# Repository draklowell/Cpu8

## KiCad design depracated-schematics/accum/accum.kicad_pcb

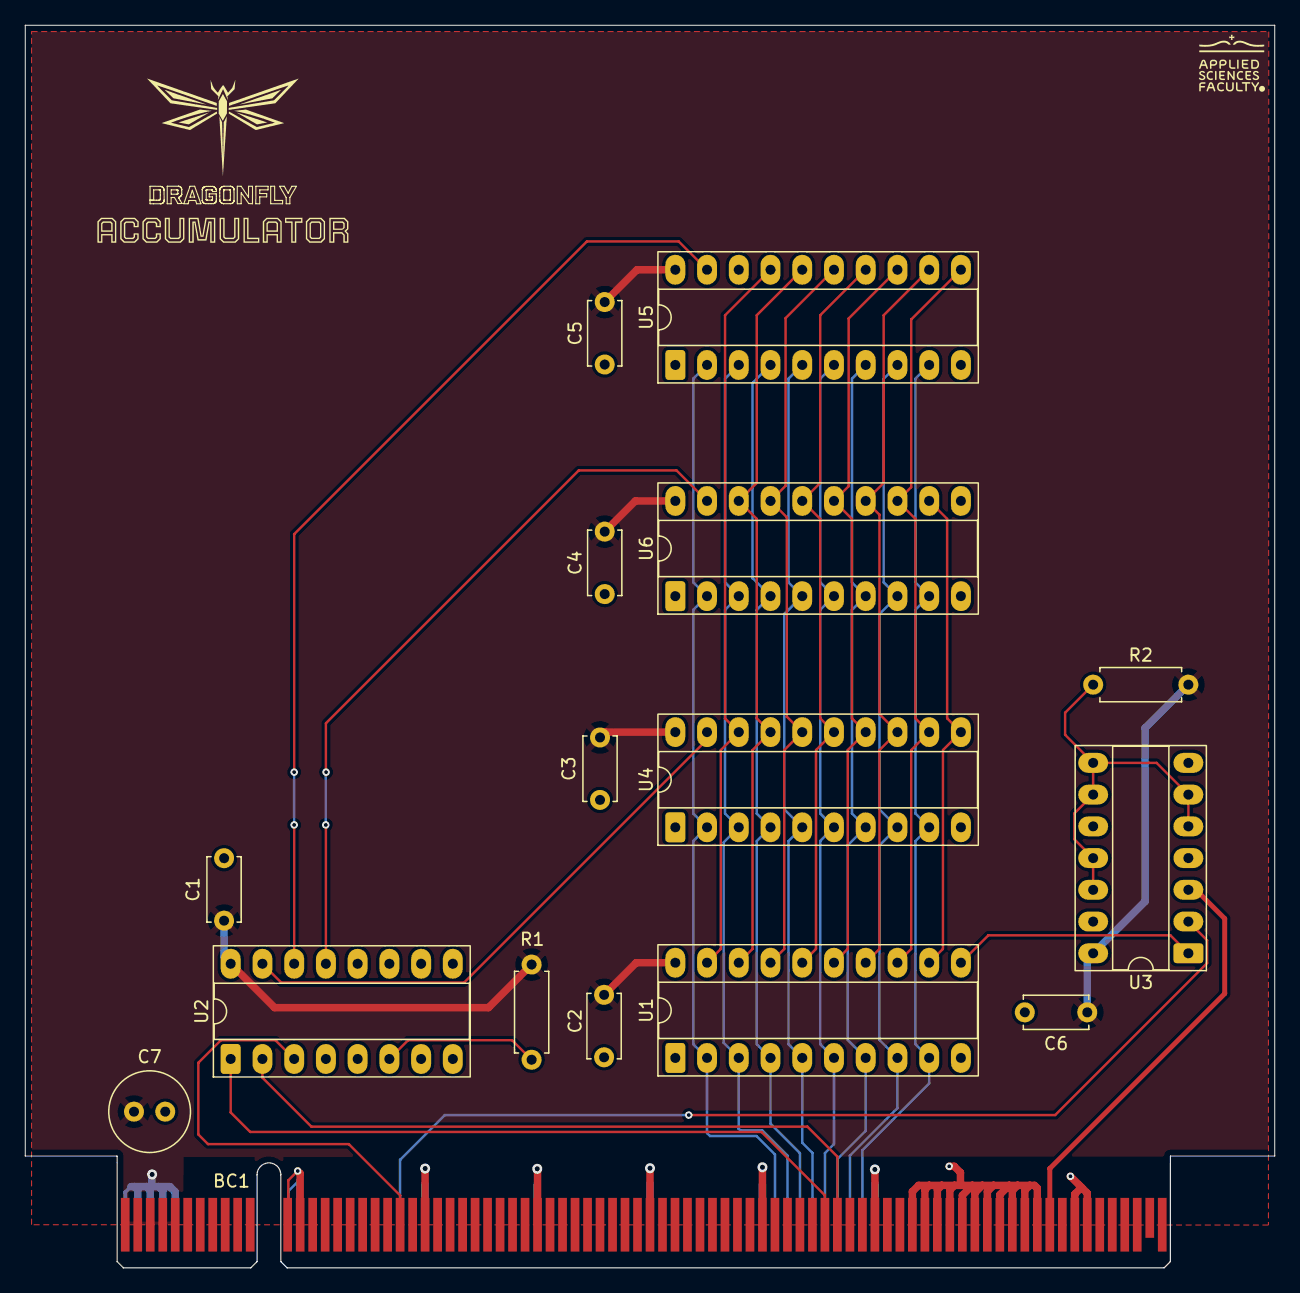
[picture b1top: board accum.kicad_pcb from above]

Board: 2 copper layers, 100.0 x 99.4 mm, 17 parts (0 on the bottom side), 29 nets.

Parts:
BC1: BusConnector; BUS_PCIexpress_x16
C1, C2, C3, C4, C5, C6: C; C_Disc_D5.0mm_W2.5mm_P5.00mm
C7: C; C_Radial_D6.3mm_H5.0mm_P2.50mm
R1, R2: R; R_Axial_DIN0207_L6.3mm_D2.5mm_P7.62mm_Horizontal
U1: 74LS574; DIP-20_W7.62mm_Socket_LongPads
U2: 74LS138; DIP-16_W7.62mm_Socket_LongPads
U3: 74LS02; DIP-14_W7.62mm_Socket_LongPads
U4, U5, U6: 74LS245; DIP-20_W7.62mm_Socket_LongPads
kibuzzard-6911C8C8: G***; kibuzzard-6911C8C8

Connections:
/ACCUM0: U1.19 (Q0), U4.18 (B0), U5.17 (B1)
/ACCUM1: U1.18 (Q1), U4.17 (B1), U5.16 (B2), U6.18 (B0)
/ACCUM2: U1.17 (Q2), U4.16 (B2), U5.15 (B3), U6.17 (B1)
/ACCUM3: U1.16 (Q3), U4.15 (B3), U5.14 (B4), U6.16 (B2)
/ACCUM4: U1.15 (Q4), U4.14 (B4), U5.13 (B5), U6.15 (B3)
/ACCUM5: U1.14 (Q5), U4.13 (B5), U5.12 (B6), U6.14 (B4)
/ACCUM6: U1.13 (Q6), U4.12 (B6), U5.11 (B7), U6.13 (B5)
/ACCUM7: U1.12 (Q7), U4.11 (B7), U6.12 (B6)
/ACSHLEFT: U2.14 (O1), U5.19 (CE)
/ACSHRIGHT: U2.13 (O2), U6.19 (CE)
/DATA0: BC1.A51 (DATA0), U1.2 (D0), U4.2 (A0), U5.2 (A0), U6.2 (A0)
/DATA1: BC1.A52 (DATA1), U1.3 (D1), U4.3 (A1), U5.3 (A1), U6.3 (A1)
/DATA2: BC1.A53 (DATA2), U1.4 (D2), U4.4 (A2), U5.4 (A2), U6.4 (A2)
/DATA3: BC1.A54 (DATA3), U1.5 (D3), U4.5 (A3), U5.5 (A3), U6.5 (A3)
/DATA4: BC1.A55 (DATA4), U1.6 (D4), U4.6 (A4), U5.6 (A4), U6.6 (A4)
/DATA5: BC1.A56 (DATA5), U1.7 (D5), U4.7 (A5), U5.7 (A5), U6.7 (A5)
/DATA6: BC1.A57 (DATA6), U1.8 (D6), U4.8 (A6), U5.8 (A6), U6.8 (A6)
/DATA7: BC1.A58 (DATA7), U1.9 (D7), U4.9 (A7), U5.9 (A7), U6.9 (A7)
/LAC: BC1.A21 (~LAC), U3.2
/SHL: BC1.B55 (ACSHLEFT), U2.1 (A0)
/SHR: BC1.B56 (ACSHRIGHT), U2.2 (A1)
/~CLK: BC1.B73 (~CLK), U3.3
/~PASS: BC1.B21 (~RAC), U2.3 (A2)
/~RAC: U2.15 (O0), U4.19 (CE)
GND: BC1.A12 (GND), BC1.A13 (GND), BC1.A23 (GND), BC1.A32 (GND), BC1.A41 (GND), BC1.A50 (GND), BC1.A59 (GND), BC1.A63 (GND), BC1.A64 (GND), BC1.A65 (GND), BC1.A66 (GND), BC1.A70 (GND), BC1.A71 (GND), BC1.A72 (GND), BC1.A73 (GND), BC1.A74 (GND), BC1.A75 (GND), BC1.A76 (GND), BC1.B12 (GND), BC1.B13 (GND), BC1.B23 (GND), BC1.B32 (GND), BC1.B41 (GND), BC1.B50 (GND), BC1.B59 (GND), BC1.B62 (GND), BC1.B63 (GND), BC1.B64 (GND), BC1.B65 (GND), BC1.B66 (GND), BC1.B67 (GND), BC1.B68 (GND), BC1.B69 (GND), BC1.B70 (GND), BC1.B71 (GND), BC1.B72 (GND), BC1.B75 (GND), BC1.B76 (GND), C1.2, C2.2, C3.2, C4.2, C5.2, C6.2, C7.2, U1.1 (OE), U1.10 (GND), U2.4 (E1), U2.5 (E2), U2.8 (GND), U3.7 (GND), U4.1 (A->B), U4.10 (GND), U5.1 (A->B), U5.10 (GND), U5.18 (B0), U6.1 (A->B), U6.10 (GND), U6.11 (B7)
unnamed: R2.1, U3.5, U3.6, U3.8, U3.9, U3.11, U3.12
unnamed: U1.11 (Cp), U3.1
unnamed: R1.2, U2.6 (E3)
VCC: BC1.A1 (VCC), BC1.A2 (VCC), BC1.A3 (VCC), BC1.A4 (VCC), BC1.A5 (VCC), BC1.B1 (VCC), BC1.B2 (VCC), BC1.B3 (VCC), BC1.B4 (VCC), BC1.B5 (VCC), C1.1, C2.1, C3.1, C4.1, C5.1, C6.1, C7.1, R1.1, R2.2, U1.20 (VCC), U2.16 (VCC), U3.14 (VCC), U4.20 (VCC), U5.20 (VCC), U6.20 (VCC)

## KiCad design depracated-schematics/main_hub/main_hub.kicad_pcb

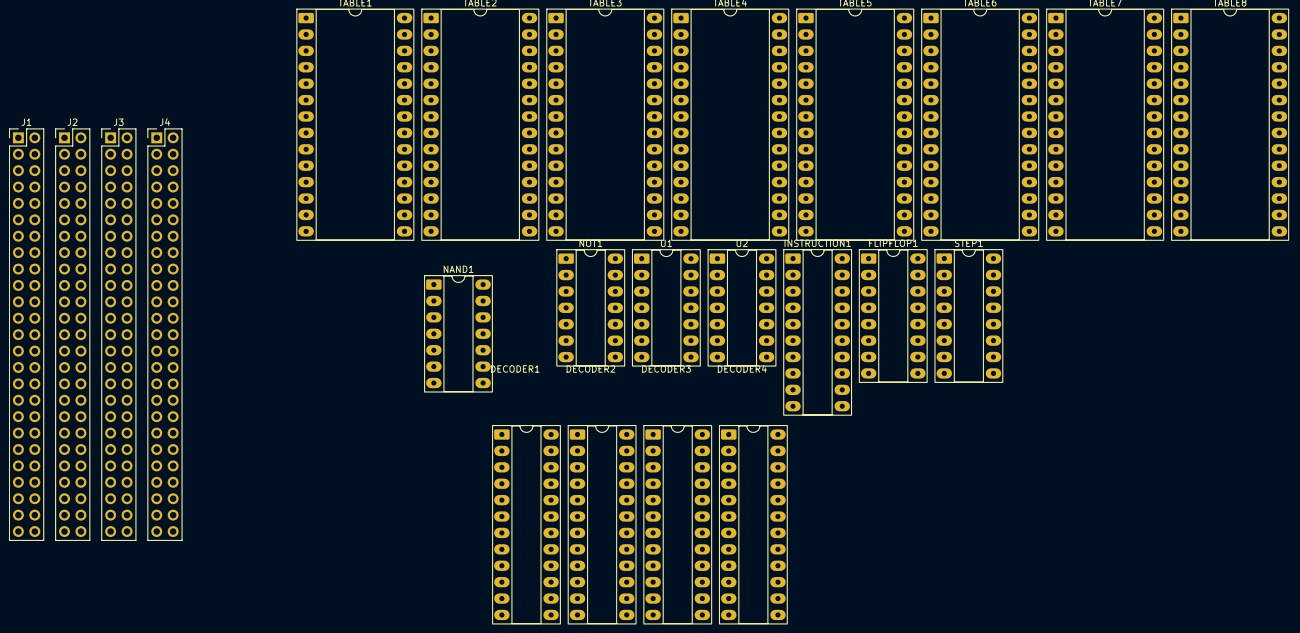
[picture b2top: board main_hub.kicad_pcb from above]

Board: 2 copper layers, 23 parts (0 on the bottom side), 99 nets, no tracks yet.

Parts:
DECODER1, DECODER2, DECODER3, DECODER4: 74LS154; DIP-24_W7.62mm_Socket_LongPads
FLIPFLOP1: 74LS109; DIP-16_W7.62mm_Socket_LongPads
INSTRUCTION1: 74LS273; DIP-20_W7.62mm_Socket_LongPads
J1, J2, J3, J4: Conn_02x25_Counter_Clockwise; PinHeader_2x25_P2.54mm_Vertical
NAND1: 74LS00; DIP-14_W7.62mm_Socket_LongPads
NOT1: 74LS04; DIP-14_W7.62mm_Socket_LongPads
STEP1: 74LS161; DIP-16_W7.62mm_Socket_LongPads
TABLE1, TABLE2, TABLE3, TABLE4, TABLE5, TABLE6, TABLE7, TABLE8: 28C256; DIP-28_W15.24mm_Socket_LongPads
U1: 74LS02; DIP-14_W7.62mm_Socket_LongPads
U2: 74LS04; DIP-14_W7.62mm_Socket_LongPads

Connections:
/ALUM: J1.31, TABLE1.17 (D5), TABLE2.17 (D5)
/ALUS0: J1.35, TABLE5.11 (D0), TABLE6.11 (D0)
/ALUS1: J1.34, TABLE5.12 (D1), TABLE6.12 (D1)
/ALUS2: J1.33, TABLE5.13 (D2), TABLE6.13 (D2)
/ALUS3: J1.32, TABLE5.15 (D3), TABLE6.15 (D3)
/ALUSignOut: J1.38, J2.23
/ALUZeroOut: J1.36, J2.21
/AccumShiftLeft: J1.29, TABLE5.18 (D6), TABLE6.18 (D6)
/AccumShiftRight: J1.28, TABLE5.19 (D7), TABLE6.19 (D7)
/AddrDecrement: TABLE7.13 (D2), TABLE8.13 (D2)
/AddrHighIn: J3.47, U2.10
/AddrIncrement: TABLE7.15 (D3), TABLE8.15 (D3)
/AddrLowIn: J3.46, U2.12
/BUS0: INSTRUCTION1.3 (D0), J1.11, J2.11, J3.11, J4.11
/BUS1: INSTRUCTION1.4 (D1), J1.12, J2.12, J3.12, J4.12
/BUS2: INSTRUCTION1.7 (D2), J1.13, J2.13, J3.13, J4.13
/BUS3: INSTRUCTION1.8 (D3), J1.14, J2.14, J3.14, J4.14
/BUS4: INSTRUCTION1.13 (D4), J1.15, J2.15, J3.15, J4.15
/BUS5: INSTRUCTION1.14 (D5), J1.16, J2.16, J3.16, J4.16
/BUS6: INSTRUCTION1.17 (D6), J1.17, J2.17, J3.17, J4.17
/BUS7: INSTRUCTION1.18 (D7), J1.18, J2.18, J3.18, J4.18
/Clk: FLIPFLOP1.4 (C), J1.4, J2.4, J3.4, J4.4, NAND1.5, NOT1.1, STEP1.2 (CP)
/IntEnable: FLIPFLOP1.2 (J), TABLE7.11 (D0), TABLE8.11 (D0)
/PCIncrement: TABLE3.19 (D7), TABLE4.19 (D7)
/Pulse: J1.48, J2.48, J3.48, J4.48, NAND1.6
/Reset: J3.34, NOT1.9
/SPDecrement: TABLE5.16 (D4), TABLE6.16 (D4)
/SPIncrement: TABLE5.17 (D5), TABLE6.17 (D5)
/STATE0: INSTRUCTION1.2 (Q0), TABLE1.10 (A0), TABLE2.10 (A0), TABLE3.10 (A0), TABLE4.10 (A0), TABLE5.10 (A0), TABLE6.10 (A0), TABLE7.10 (A0), TABLE8.10 (A0)
/STATE1: INSTRUCTION1.5 (Q1), TABLE1.9 (A1), TABLE2.9 (A1), TABLE3.9 (A1), TABLE4.9 (A1), TABLE5.9 (A1), TABLE6.9 (A1), TABLE7.9 (A1), TABLE8.9 (A1)
/STATE2: INSTRUCTION1.6 (Q2), TABLE1.8 (A2), TABLE2.8 (A2), TABLE3.8 (A2), TABLE4.8 (A2), TABLE5.8 (A2), TABLE6.8 (A2), TABLE7.8 (A2), TABLE8.8 (A2)
/STATE3: INSTRUCTION1.9 (Q3), TABLE1.7 (A3), TABLE2.7 (A3), TABLE3.7 (A3), TABLE4.7 (A3), TABLE5.7 (A3), TABLE6.7 (A3), TABLE7.7 (A3), TABLE8.7 (A3)
/STATE4: INSTRUCTION1.12 (Q4), TABLE1.6 (A4), TABLE2.6 (A4), TABLE3.6 (A4), TABLE4.6 (A4), TABLE5.6 (A4), TABLE6.6 (A4), TABLE7.6 (A4), TABLE8.6 (A4)
/STATE5: INSTRUCTION1.15 (Q5), TABLE1.5 (A5), TABLE2.5 (A5), TABLE3.5 (A5), TABLE4.5 (A5), TABLE5.5 (A5), TABLE6.5 (A5), TABLE7.5 (A5), TABLE8.5 (A5)
/STATE6: INSTRUCTION1.16 (Q6), TABLE1.4 (A6), TABLE2.4 (A6), TABLE3.4 (A6), TABLE4.4 (A6), TABLE5.4 (A6), TABLE6.4 (A6), TABLE7.4 (A6), TABLE8.4 (A6)
/STATE7: INSTRUCTION1.19 (Q7), TABLE1.3 (A7), TABLE2.3 (A7), TABLE3.3 (A7), TABLE4.3 (A7), TABLE5.3 (A7), TABLE6.3 (A7), TABLE7.3 (A7), TABLE8.3 (A7)
/STATE8: J2.44, TABLE1.25 (A8), TABLE2.25 (A8), TABLE3.25 (A8), TABLE4.25 (A8), TABLE5.25 (A8), TABLE6.25 (A8), TABLE7.25 (A8), TABLE8.25 (A8)
/STATE9: J2.45, TABLE1.24 (A9), TABLE2.24 (A9), TABLE3.24 (A9), TABLE4.24 (A9), TABLE5.24 (A9), TABLE6.24 (A9), TABLE7.24 (A9), TABLE8.24 (A9)
/STATE10: J2.46, TABLE1.21 (A10), TABLE2.21 (A10), TABLE3.21 (A10), TABLE4.21 (A10), TABLE5.21 (A10), TABLE6.21 (A10), TABLE7.21 (A10), TABLE8.21 (A10)
/STATE11: STEP1.14 (Q0), TABLE1.23 (A11), TABLE2.23 (A11), TABLE3.23 (A11), TABLE4.23 (A11), TABLE5.23 (A11), TABLE6.23 (A11), TABLE7.23 (A11), TABLE8.23 (A11)
/STATE12: STEP1.13 (Q1), TABLE1.2 (A12), TABLE2.2 (A12), TABLE3.2 (A12), TABLE4.2 (A12), TABLE5.2 (A12), TABLE6.2 (A12), TABLE7.2 (A12), TABLE8.2 (A12)
/STATE13: STEP1.12 (Q2), TABLE1.26 (A13), TABLE2.26 (A13), TABLE3.26 (A13), TABLE4.26 (A13), TABLE5.26 (A13), TABLE6.26 (A13), TABLE7.26 (A13), TABLE8.26 (A13)
/STATE14: STEP1.11 (Q3), TABLE1.1 (A14), TABLE2.1 (A14), TABLE3.1 (A14), TABLE4.1 (A14), TABLE5.1 (A14), TABLE6.1 (A14), TABLE7.1 (A14), TABLE8.1 (A14)
/STATE15: NOT1.6, TABLE1.22 (~OE), TABLE3.22 (~OE), TABLE5.22 (~OE), TABLE7.22 (~OE)
/STATE16: NAND1.3, NOT1.5, TABLE2.22 (~OE), TABLE4.22 (~OE), TABLE6.22 (~OE), TABLE8.22 (~OE)
/Wait: J3.37, NOT1.3
/~ALUCarryIn: J1.30, TABLE1.18 (D6), TABLE2.18 (D6)
/~ALUCarryOut: J1.37, J2.22
/~ALUWriter: DECODER4.1 (S0), J1.39
/~AccumReader: DECODER1.9 (S8), J1.46
/~AccumWriter: DECODER3.9 (S8), J1.27
/~AddressHighReader: DECODER2.1 (S0), U2.11
/~AddressLowReader: DECODER2.2 (S1), U2.13
/~Clk: J1.3, J2.3, J3.3, J4.3, NOT1.2, NOT1.13, U1.2
/~FlagsReader: DECODER1.16 (S14), J2.34
/~FlagsUpdate: J2.28, TABLE1.19 (D7), TABLE2.19 (D7)
/~FlagsWriter: DECODER3.16 (S14), J2.40
/~Halt: NAND1.13, TABLE3.18 (D6), TABLE4.18 (D6)
/~InstructionReader: DECODER1.17 (S15), U1.3
/~IntDisable: FLIPFLOP1.3 (~K), TABLE7.12 (D1), TABLE8.12 (D1)
/~PCHighReader: DECODER1.5 (S4), U2.5
/~PCLowReader: DECODER1.6 (S5), U2.9
/~Reset: FLIPFLOP1.5 (~S), INSTRUCTION1.1 (~Mr), NOT1.8, STEP1.1 (~MR)
/~SCClear: STEP1.9 (~PE), TABLE3.17 (D5), TABLE4.17 (D5)
/~SPHighReader: DECODER1.3 (S2), U2.1
/~SPLowReader: DECODER1.4 (S3), U2.3
/~TemporaryHighReader: DECODER1.7 (S6), J1.40
/~TemporaryHighWriter: DECODER3.7 (S6), J1.41
/~XHReader: DECODER1.10 (S9), J2.33
/~XHWriter: DECODER3.10 (S9), J2.39
/~YHReader: DECODER1.13 (S11), J2.31
/~YHWriter: DECODER3.13 (S11), J2.37
/~YLReader: DECODER1.11 (S10), J2.32
/~YLWriter: DECODER3.11 (S10), J2.38
/~ZHReader: DECODER1.15 (S13), J2.29
/~ZHWriter: DECODER3.15 (S13), J2.35
/~ZLReader: DECODER1.14 (S12), J2.30
/~ZLWriter: DECODER3.14 (S12), J2.36
GND: DECODER1.12 (GND), DECODER1.18 (E0), DECODER2.12 (GND), DECODER2.18 (E0), DECODER3.12 (GND), DECODER3.18 (E0), DECODER4.12 (GND), DECODER4.18 (E0), FLIPFLOP1.8 (GND), INSTRUCTION1.10 (GND), J1.2, J1.10, J1.19, J1.49, J2.2, J2.10, J2.19, J2.49, J3.2, J3.10, J3.19, J3.49, J4.2, J4.10, J4.19, J4.49, NAND1.7 (GND), NOT1.7 (GND), STEP1.3 (D0), STEP1.4 (D1), STEP1.5 (D2), STEP1.6 (D3), STEP1.8 (GND), TABLE1.14 (GND), TABLE1.20 (~CS), TABLE1.27 (~WE), TABLE2.14 (GND), TABLE2.20 (~CS), TABLE2.27 (~WE), TABLE3.14 (GND), TABLE3.20 (~CS), TABLE3.27 (~WE), TABLE4.14 (GND), TABLE4.20 (~CS), TABLE4.27 (~WE), TABLE5.14 (GND), TABLE5.20 (~CS), TABLE5.27 (~WE), TABLE6.14 (GND), TABLE6.20 (~CS), TABLE6.27 (~WE), TABLE7.14 (GND), TABLE7.20 (~CS), TABLE7.27 (~WE), TABLE8.14 (GND), TABLE8.20 (~CS), TABLE8.27 (~WE), U1.7 (GND), U2.7 (GND)
unnamed: DECODER1.23 (A0), DECODER2.23 (A0), TABLE1.12 (D1), TABLE2.12 (D1)
unnamed: DECODER1.22 (A1), DECODER2.22 (A1), TABLE1.13 (D2), TABLE2.13 (D2)
unnamed: DECODER1.21 (A2), DECODER2.21 (A2), TABLE1.15 (D3), TABLE2.15 (D3)
unnamed: DECODER1.20 (A3), DECODER2.20 (A3), TABLE1.16 (D4), TABLE2.16 (D4)
unnamed: DECODER1.19 (E1), U1.10
unnamed: DECODER2.19 (E1), TABLE1.11 (D0), TABLE2.11 (D0), U1.8, U1.9
unnamed: DECODER3.23 (A0), DECODER4.23 (A0), TABLE3.12 (D1), TABLE4.12 (D1)
unnamed: DECODER3.22 (A1), DECODER4.22 (A1), TABLE3.13 (D2), TABLE4.13 (D2)
unnamed: DECODER3.21 (A2), DECODER4.21 (A2), TABLE3.15 (D3), TABLE4.15 (D3)
unnamed: DECODER3.20 (A3), DECODER4.20 (A3), TABLE3.16 (D4), TABLE4.16 (D4)
unnamed: DECODER3.19 (E1), U1.4
unnamed: DECODER4.19 (E1), TABLE3.11 (D0), TABLE4.11 (D0), U1.5, U1.6
unnamed: FLIPFLOP1.6 (Q), NAND1.1
unnamed: INSTRUCTION1.11 (Cp), U1.1
unnamed: NAND1.4, NOT1.10
unnamed: NAND1.9, NAND1.10, NAND1.11
unnamed: NAND1.12, NOT1.4
unnamed: NOT1.11, NOT1.12
unnamed: NAND1.8, STEP1.7 (CEP), STEP1.10 (CET)
VCC: DECODER1.24 (VCC), DECODER2.24 (VCC), DECODER3.24 (VCC), DECODER4.24 (VCC), FLIPFLOP1.16 (VCC), INSTRUCTION1.20 (VCC), J1.1, J1.25, J1.26, J1.50, J2.1, J2.25, J2.26, J2.50, J3.1, J3.25, J3.26, J3.50, J4.1, J4.25, J4.26, J4.50, NAND1.14 (VCC), NOT1.14 (VCC), STEP1.16 (VCC), TABLE1.28 (VCC), TABLE2.28 (VCC), TABLE3.28 (VCC), TABLE4.28 (VCC), TABLE5.28 (VCC), TABLE6.28 (VCC), TABLE7.28 (VCC), TABLE8.28 (VCC), U1.14 (VCC), U2.14 (VCC)

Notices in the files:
parts and their libraries:
License: Apache-2.0
